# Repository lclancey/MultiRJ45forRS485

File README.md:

# MultiRJ45 for RS485

## Description

A simple RS485 connector design.

* Install on TH35-7.5(C45) DIN rail.
* Using CAT5e Shielded Twisted Pair(STP) cable. 
  * Earth pin will connect to DIN rail for better transmission quality.
* Support 4-port RJ45 socket.

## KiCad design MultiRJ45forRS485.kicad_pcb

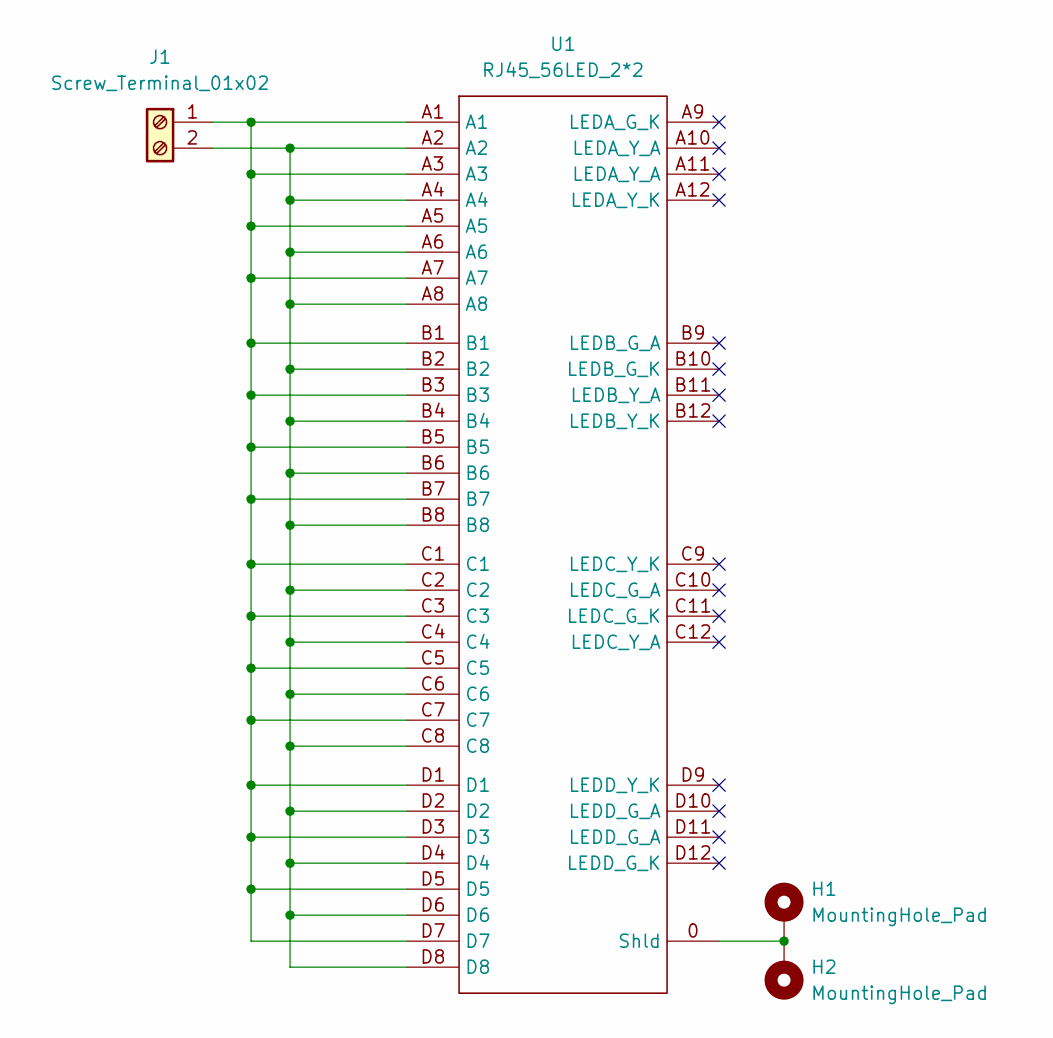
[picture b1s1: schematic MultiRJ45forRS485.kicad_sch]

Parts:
H1, H2: MountingHole_Pad; MountingHole_4.3mm_M4_DIN965_Pad_TopOnly
J1: Screw_Terminal_01x02; TerminalBlock_Altech_AK300-2_P5.00mm
U1: RJ45_56LED_2*2

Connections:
unnamed: H1.1, H2.1, U1.0 (Shld)
unnamed: J1.1, U1.A1, U1.A3, U1.A5, U1.A7, U1.B1, U1.B3, U1.B5, U1.B7, U1.C1, U1.C3, U1.C5, U1.C7, U1.D1, U1.D3, U1.D5, U1.D7
unnamed: J1.2, U1.A2, U1.A4, U1.A6, U1.A8, U1.B2, U1.B4, U1.B6, U1.B8, U1.C2, U1.C4, U1.C6, U1.C8, U1.D2, U1.D4, U1.D6, U1.D8

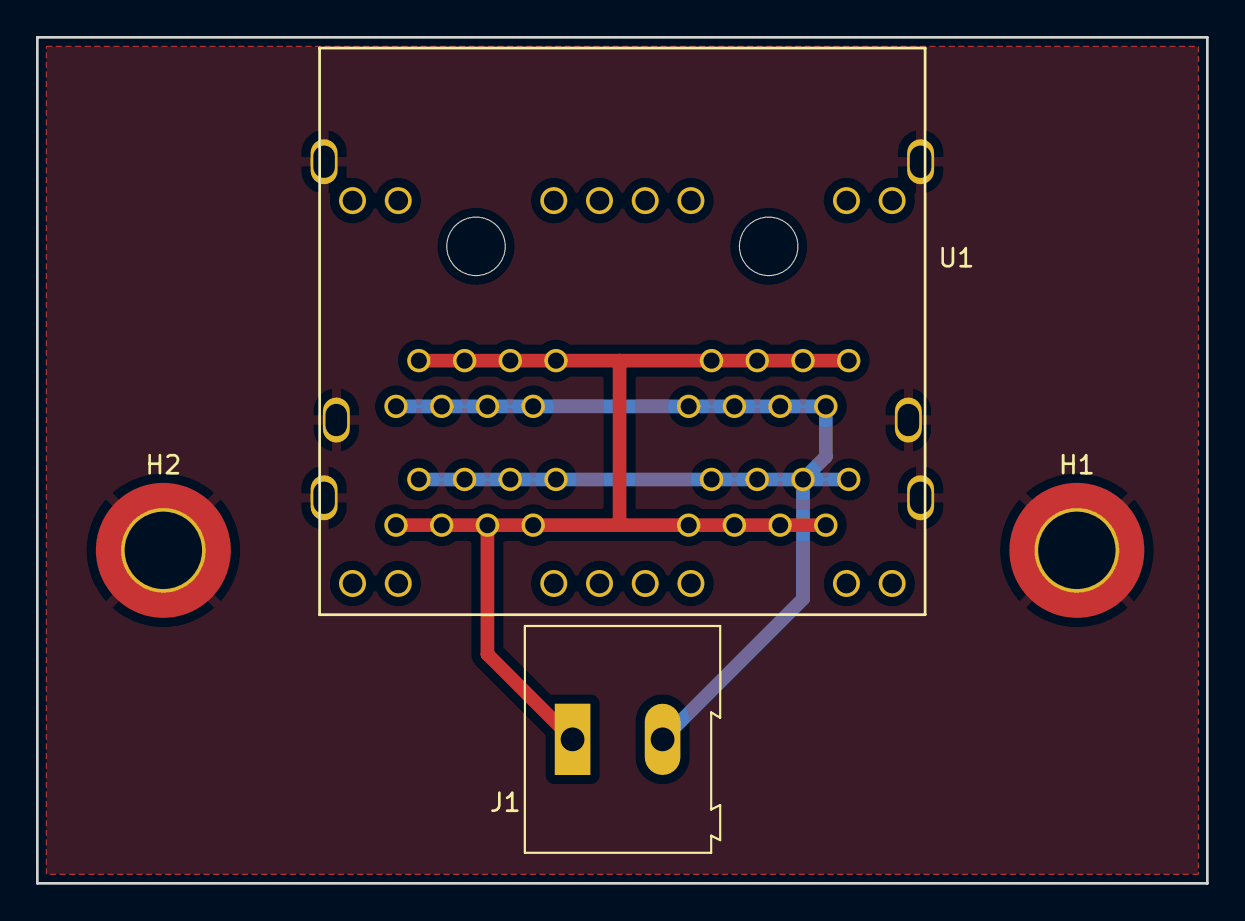
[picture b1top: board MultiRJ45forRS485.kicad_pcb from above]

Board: 2 copper layers, 65.0 x 47.0 mm, 4 parts (0 on the bottom side), 3 nets.

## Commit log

2022-01-18 init
2022-01-18 Create PCB
